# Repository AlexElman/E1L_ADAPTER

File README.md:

# E1L_ADAPTER
PCIE 3.0 adapter for a Samsung Datacenter 15.36 TB E1L SSD

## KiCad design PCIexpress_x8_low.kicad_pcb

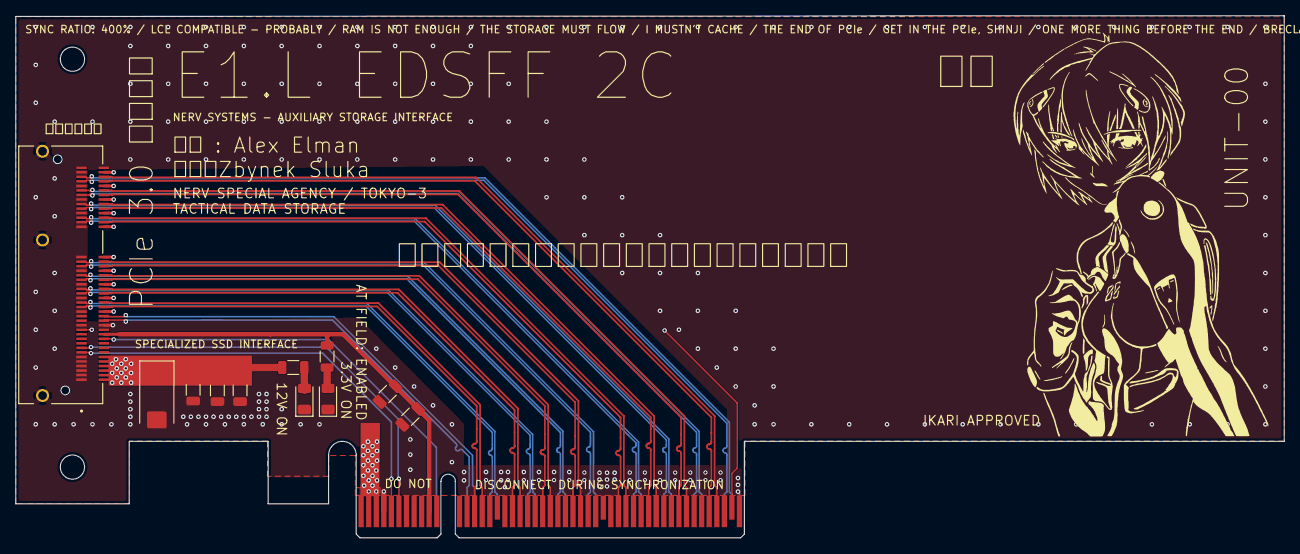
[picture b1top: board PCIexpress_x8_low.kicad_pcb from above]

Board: 4 copper layers, 167.7 x 69.0 mm, 12 parts (0 on the bottom side), 44 nets.

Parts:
C18, C19, C22, C23: 10uF; C_1206_3216Metric
C20: 100uF; CP_EIA-7343-30_AVX-N_HandSolder
C21: 0.1uF; C_1206_3216Metric
D1, D2: LED; LED_1206_3216Metric
J2: PCIexpress_x8
J3: ME1008410201031; AMPHENOL_ME1008410201031
R1: 2,2KR; R_1206_3216Metric
R2: 150R; R_1206_3216Metric

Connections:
+3.3VA: C22.1, C23.1, J2.B10 (+3.3V_aux), J3.B11, R2.2
+3V3: J2.A9 (+3.3V), J2.A10 (+3.3V), J2.B8 (+3.3V)
+12V: C18.1, C19.1, C20.1, C21.1, J2.A2 (+12V), J2.A3 (+12V), J2.B1 (+12V), J2.B2 (+12V), J2.B3 (+12V), J3.B1, J3.B2, J3.B3, J3.B4, J3.B5, J3.B6, R1.2
/PER0_N: J2.A17 (PERn0), J3.A18
/PER0_P: J2.A16 (PERp0), J3.A17
/PER1_N: J2.A22 (PERn1), J3.A21
/PER1_P: J2.A21 (PERp1), J3.A20
/PER2_N: J2.A26 (PERn2), J3.A24
/PER2_P: J2.A25 (PERp2), J3.A23
/PER3_N: J2.A30 (PERn3), J3.A27
/PER3_P: J2.A29 (PERp3), J3.A26
/PER4_N: J2.A36 (PERn4), J3.A31
/PER4_P: J2.A35 (PERp4), J3.A30
/PER5_N: J2.A40 (PERn5), J3.A34
/PER5_P: J2.A39 (PERp5), J3.A33
/PER6_N: J2.A44 (PERn6), J3.A37
/PER6_P: J2.A43 (PERp6), J3.A36
/PER7_N: J2.A48 (PERn7), J3.A40
/PER7_P: J2.A47 (PERp7), J3.A39
/PET0_N: J2.B15 (PETn0), J3.B18
/PET0_P: J2.B14 (PETp0), J3.B17
/PET1_N: J2.B20 (PETn1), J3.B21
/PET1_P: J2.B19 (PETp1), J3.B20
/PET2_N: J2.B24 (PETn2), J3.B24
/PET2_P: J2.B23 (PETp2), J3.B23
/PET3_N: J2.B28 (PETn3), J3.B27
/PET3_P: J2.B27 (PETp3), J3.B26
/PET4_N: J2.B34 (PETn4), J3.B31
/PET4_P: J2.B33 (PETp4), J3.B30
/PET5_N: J2.B38 (PETn5), J3.B34
/PET5_P: J2.B37 (PETp5), J3.B33
/PET6_N: J2.B42 (PETn6), J3.B37
/PET6_P: J2.B41 (PETp6), J3.B36
/PET7_N: J2.B46 (PETn7), J3.B40
/PET7_P: J2.B45 (PETp7), J3.B39
/REFCLK+: J2.A13 (REFCLK+), J3.B14
/REFCLK-: J2.A14 (REFCLK-), J3.B15
/SMCLK: J2.B5 (SMCLK), J3.A7
/SMDAT: J2.B6 (SMDAT), J3.A8
/~PERST: J2.A11 (~PERST), J3.B10
/~PRSNT2x8: J2.B48 (~PRSNT2), J3.A12
GND: C18.2, C19.2, C20.2, C21.2, C22.2, C23.2, D1.1 (K), D2.1 (K), J2.A4 (GND), J2.A12 (GND), J2.A15 (GND), J2.A18 (GND), J2.A20 (GND), J2.A23 (GND), J2.A24 (GND), J2.A27 (GND), J2.A28 (GND), J2.A31 (GND), J2.A34 (GND), J2.A37 (GND), J2.A38 (GND), J2.A41 (GND), J2.A42 (GND), J2.A45 (GND), J2.A46 (GND), J2.A49 (GND), J2.B4 (GND), J2.B7 (GND), J2.B13 (GND), J2.B16 (GND), J2.B18 (GND), J2.B21 (GND), J2.B22 (GND), J2.B25 (GND), J2.B26 (GND), J2.B29 (GND), J2.B32 (GND), J2.B35 (GND), J2.B36 (GND), J2.B39 (GND), J2.B40 (GND), J2.B43 (GND), J2.B44 (GND), J2.B47 (GND), J2.B49 (GND), J3.A1, J3.A2, J3.A3, J3.A4, J3.A5, J3.A6, J3.A13, J3.A16, J3.A19, J3.A22, J3.A25, J3.A28, J3.A29, J3.A32, J3.A35, J3.A38, J3.A41, J3.B13, J3.B16, J3.B19, J3.B22, J3.B25, J3.B28, J3.B29, J3.B32, J3.B35, J3.B38, J3.B41, J3.SH1 (SHIELD), J3.SH2 (SHIELD__1), J3.SH3 (SHIELD__2)
unnamed: D1.2 (A), R1.1
unnamed: D2.2 (A), R2.1

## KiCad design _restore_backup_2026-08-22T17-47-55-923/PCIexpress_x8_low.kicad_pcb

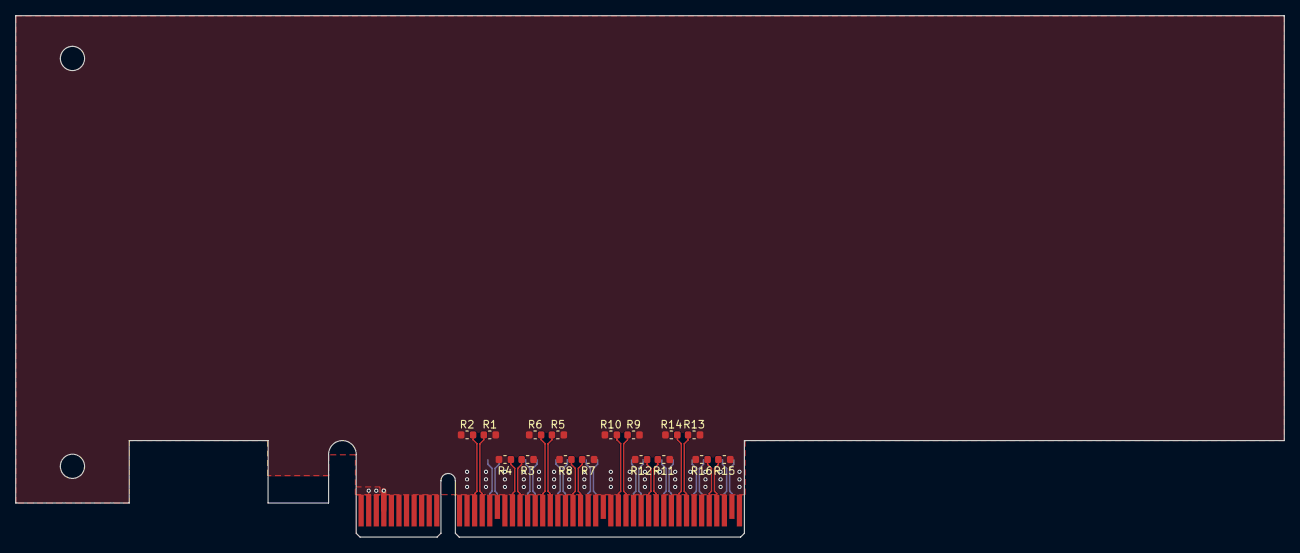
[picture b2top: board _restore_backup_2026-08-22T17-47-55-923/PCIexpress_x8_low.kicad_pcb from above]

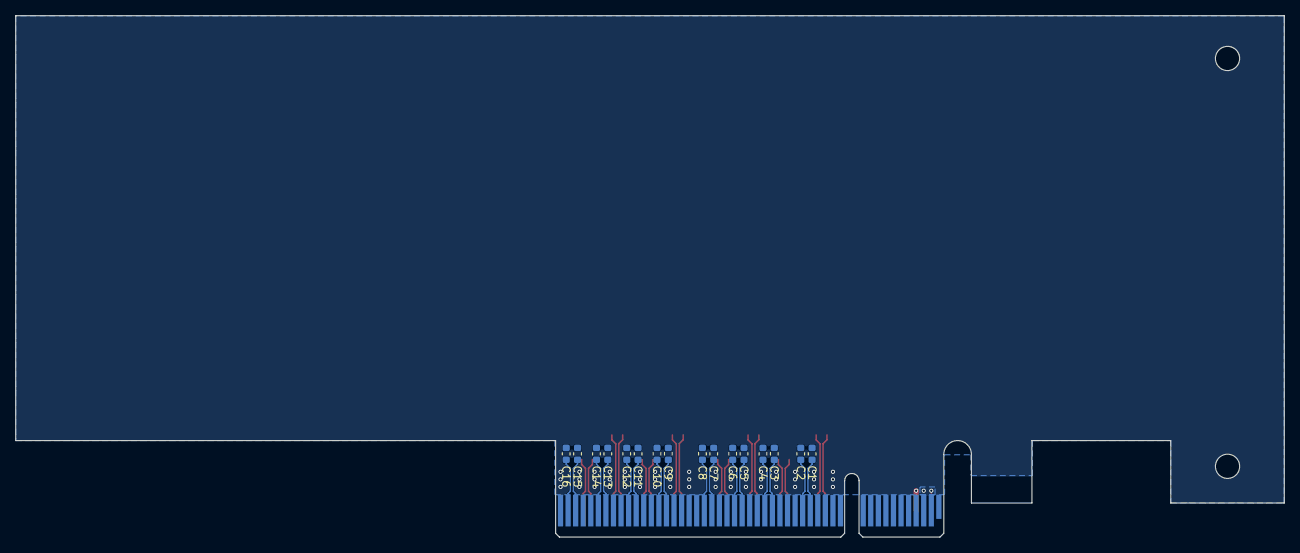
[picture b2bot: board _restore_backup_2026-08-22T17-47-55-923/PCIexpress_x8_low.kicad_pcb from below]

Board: 4 copper layers, 167.7 x 68.9 mm, 34 parts (16 on the bottom side), 35 nets.

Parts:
C1, C2, C3, C4, C5, C6, C7, C8, C9, C10, C11, C12, C13, C14, C15, C16: 100n; C_0603_1608Metric
J1: PCIexpress_bracket; PCIexpress_bracket_low
J2: PCIexpress_x8
R1, R2, R3, R4, R5, R6, R7, R8, R9, R10, R11, R12, R13, R14, R15, R16: 49.9; R_0603_1608Metric

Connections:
+3V3: J2.A9 (+3.3V), J2.A10 (+3.3V), J2.B8 (+3.3V)
+12V: J2.A2 (+12V), J2.A3 (+12V), J2.B1 (+12V), J2.B2 (+12V), J2.B3 (+12V)
/PCIexpress_connector/_PER0_N: C2.1, J2.A17 (PERn0)
/PCIexpress_connector/_PER0_P: C1.2, J2.A16 (PERp0)
/PCIexpress_connector/_PER1_N: C4.1, J2.A22 (PERn1)
/PCIexpress_connector/_PER1_P: C3.2, J2.A21 (PERp1)
/PCIexpress_connector/_PER2_N: C6.1, J2.A26 (PERn2)
/PCIexpress_connector/_PER2_P: C5.2, J2.A25 (PERp2)
/PCIexpress_connector/_PER3_N: C8.1, J2.A30 (PERn3)
/PCIexpress_connector/_PER3_P: C7.2, J2.A29 (PERp3)
/PCIexpress_connector/_PER4_N: C10.1, J2.A36 (PERn4)
/PCIexpress_connector/_PER4_P: C9.2, J2.A35 (PERp4)
/PCIexpress_connector/_PER5_N: C12.1, J2.A40 (PERn5)
/PCIexpress_connector/_PER5_P: C11.2, J2.A39 (PERp5)
/PCIexpress_connector/_PER6_N: C14.1, J2.A44 (PERn6)
/PCIexpress_connector/_PER6_P: C13.2, J2.A43 (PERp6)
/PCIexpress_connector/_PER7_N: C16.1, J2.A48 (PERn7)
/PCIexpress_connector/_PER7_P: C15.2, J2.A47 (PERp7)
/PET0_N: J2.B15 (PETn0), R1.1
/PET0_P: J2.B14 (PETp0), R2.1
/PET1_N: J2.B20 (PETn1), R3.1
/PET1_P: J2.B19 (PETp1), R4.1
/PET2_N: J2.B24 (PETn2), R5.1
/PET2_P: J2.B23 (PETp2), R6.1
/PET3_N: J2.B28 (PETn3), R7.1
/PET3_P: J2.B27 (PETp3), R8.1
/PET4_N: J2.B34 (PETn4), R9.1
/PET4_P: J2.B33 (PETp4), R10.1
/PET5_N: J2.B38 (PETn5), R11.1
/PET5_P: J2.B37 (PETp5), R12.1
/PET6_N: J2.B42 (PETn6), R13.1
/PET6_P: J2.B41 (PETp6), R14.1
/PET7_N: J2.B46 (PETn7), R15.1
/PET7_P: J2.B45 (PETp7), R16.1
GND: J2.A4 (GND), J2.A12 (GND), J2.A15 (GND), J2.A18 (GND), J2.A20 (GND), J2.A23 (GND), J2.A24 (GND), J2.A27 (GND), J2.A28 (GND), J2.A31 (GND), J2.A34 (GND), J2.A37 (GND), J2.A38 (GND), J2.A41 (GND), J2.A42 (GND), J2.A45 (GND), J2.A46 (GND), J2.A49 (GND), J2.B4 (GND), J2.B7 (GND), J2.B13 (GND), J2.B16 (GND), J2.B18 (GND), J2.B21 (GND), J2.B22 (GND), J2.B25 (GND), J2.B26 (GND), J2.B29 (GND), J2.B32 (GND), J2.B35 (GND), J2.B36 (GND), J2.B39 (GND), J2.B40 (GND), J2.B43 (GND), J2.B44 (GND), J2.B47 (GND), J2.B49 (GND), R1.2, R2.2, R3.2, R4.2, R5.2, R6.2, R7.2, R8.2, R9.2, R10.2, R11.2, R12.2, R13.2, R14.2, R15.2, R16.2
